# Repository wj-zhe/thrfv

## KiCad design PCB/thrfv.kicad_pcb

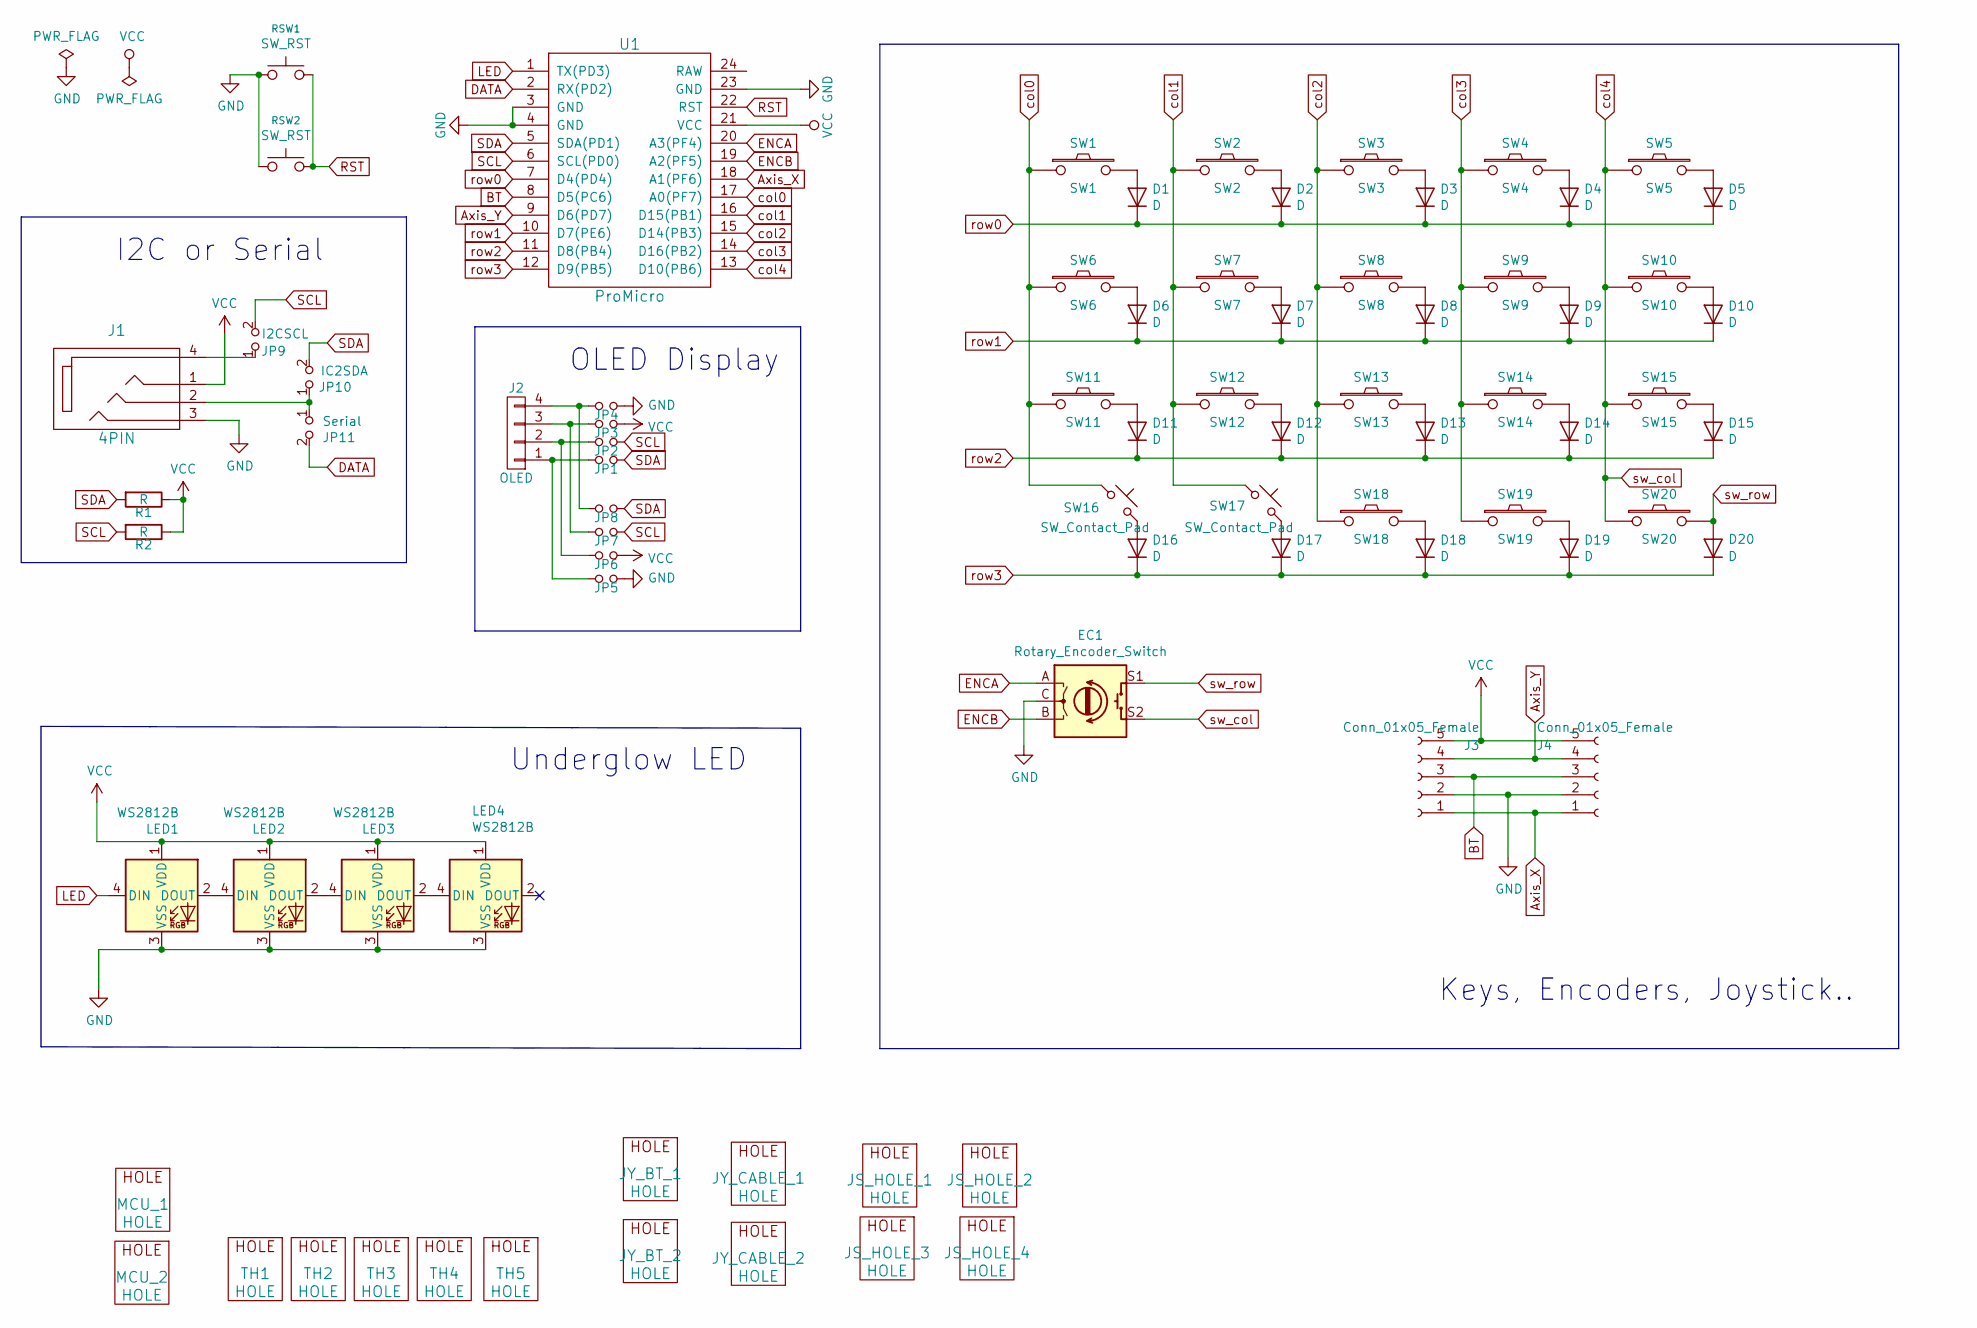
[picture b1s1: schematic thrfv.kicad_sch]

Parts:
D1, D2, D3, D4, D5, D6, D7, D8, D9, D10, D11, D12, D13, D14, D15, D16, D17, D18, D19, D20: D; Diode_SOD123_THT_2
EC1: Rotary_Encoder_Switch; RotaryEncoder_Alps_EC11E-Switch_Vertical_H20mm
J1: 4PIN; MJ-4PP-9
J2: OLED; OLED_4Pin
J3, J4: Conn_01x05_Female; TE_0-1734839-5_1x05-1MP_P0.5mm_Horizontal
JP1: JP1; SolderJumper-2_P1.3mm_Open_RoundedPad1.0x1.5mm
JP2: JP2; SolderJumper-2_P1.3mm_Open_RoundedPad1.0x1.5mm
JP3: JP3; SolderJumper-2_P1.3mm_Open_RoundedPad1.0x1.5mm
JP4: JP4; SolderJumper-2_P1.3mm_Open_RoundedPad1.0x1.5mm
JP5: JP5; SolderJumper-2_P1.3mm_Open_RoundedPad1.0x1.5mm
JP6: JP6; SolderJumper-2_P1.3mm_Open_RoundedPad1.0x1.5mm
JP7: JP7; SolderJumper-2_P1.3mm_Open_RoundedPad1.0x1.5mm
JP8: JP8; SolderJumper-2_P1.3mm_Open_RoundedPad1.0x1.5mm
JP9: I2CSCL; SolderJumper-2_P1.3mm_Open_RoundedPad1.0x1.5mm
JP10: IC2SDA; SolderJumper-2_P1.3mm_Open_RoundedPad1.0x1.5mm
JP11: Serial; SolderJumper-2_P1.3mm_Open_RoundedPad1.0x1.5mm
JS_HOLE_1, JS_HOLE_2, JS_HOLE_3, JS_HOLE_4: HOLE; MountingHole_2.7mm_M2.5
JY_BT_1, JY_BT_2: HOLE; MountingHole_3.2mm_M3
JY_CABLE_1, JY_CABLE_2: HOLE; Mounting_Hole_7x3mm
LED1, LED2, LED3, LED4: WS2812B; LED_WS2812B_PLCC4_5.0x5.0mm_P3.2mm_double_side
MCU_1, MCU_2: HOLE; MountingHole_2.2mm_M2_Pad
R1, R2: R; R_1206_DoubleSided
RSW1, RSW2: SW_RST; SW_SPST_TL3342
SW1: SW1; CherryMX_Hotswap
SW2: SW2; CherryMX_Hotswap
SW3: SW3; CherryMX_Hotswap
SW4: SW4; CherryMX_Hotswap
SW5: SW5; CherryMX_Hotswap
SW6: SW6; CherryMX_Hotswap
SW7: SW7; CherryMX_Hotswap
SW8: SW8; CherryMX_Hotswap
SW9: SW9; CherryMX_Hotswap
SW10: SW10; CherryMX_Hotswap
SW11: SW11; CherryMX_Hotswap
SW12: SW12; CherryMX_Hotswap
SW13: SW13; CherryMX_Hotswap
SW14: SW14; CherryMX_Hotswap
SW15: SW15; CherryMX_Hotswap
SW16, SW17: SW_Contact_Pad; contact_button_pad_half_circle_3mm
SW18: SW18; CherryMX_Hotswap
SW19: SW19; CherryMX_Hotswap
SW20: SW20; CherryMX_Hotswap
TH1, TH2, TH3, TH4, TH5: HOLE; MountingHole_3.2mm_M3
U1: ProMicro; ProMicro_jumper_pad_only

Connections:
Axis_X: J3.1, J4.1, U1.18 (A1(PF6))
Axis_Y: J3.4, J4.4, U1.9 (D6(PD7))
BT: J3.3, J4.3, U1.8 (D5(PC6))
DATA: JP11.2, U1.2 (RX(PD2))
ENCA: EC1.A, U1.20 (A3(PF4))
ENCB: EC1.B, U1.19 (A2(PF5))
GND: EC1.C, J1.3, J3.2, J4.2, JP4.2, JP5.2, LED1.3 (VSS), LED2.3 (VSS), LED3.3 (VSS), LED4.3 (VSS), RSW1.1, RSW2.1, U1.3 (GND), U1.4 (GND), U1.23 (GND)
LED: LED1.4 (DIN), U1.1 (TX(PD3))
unnamed: D1.2 (A), SW1.2
unnamed: D2.2 (A), SW2.2
unnamed: D3.2 (A), SW3.2
unnamed: D4.2 (A), SW4.2
unnamed: D5.2 (A), SW5.2
unnamed: D6.2 (A), SW6.2
unnamed: D7.2 (A), SW7.2
unnamed: D8.2 (A), SW8.2
unnamed: D9.2 (A), SW9.2
unnamed: D10.2 (A), SW10.2
unnamed: D11.2 (A), SW11.2
unnamed: D12.2 (A), SW12.2
unnamed: D13.2 (A), SW13.2
unnamed: D14.2 (A), SW14.2
unnamed: D15.2 (A), SW15.2
unnamed: D16.2 (A), SW16.2
unnamed: D17.2 (A), SW17.2
unnamed: D18.2 (A), SW18.2
unnamed: D19.2 (A), SW19.2
unnamed: J1.2, JP10.1, JP11.1
unnamed: J1.4, JP9.1
unnamed: J2.1, JP1.1, JP5.1
unnamed: J2.2, JP2.1, JP6.1
unnamed: J2.3, JP3.1, JP7.1
unnamed: J2.4, JP4.1, JP8.1
unnamed: LED1.2 (DOUT), LED2.4 (DIN)
unnamed: LED2.2 (DOUT), LED3.4 (DIN)
unnamed: LED3.2 (DOUT), LED4.4 (DIN)
RST: RSW1.2, RSW2.2, U1.22 (RST)
SCL: JP2.2, JP7.2, JP9.2, R2.2, U1.6 (SCL(PD0))
SDA: JP1.2, JP8.2, JP10.2, R1.2, U1.5 (SDA(PD1))
VCC: J1.1, J3.5, J4.5, JP3.2, JP6.2, LED1.1 (VDD), LED2.1 (VDD), LED3.1 (VDD), LED4.1 (VDD), R1.1, R2.1, U1.21 (VCC)
col0: SW1.1, SW6.1, SW11.1, SW16.1, U1.17 (A0(PF7))
col1: SW2.1, SW7.1, SW12.1, SW17.1, U1.16 (D15(PB1))
col2: SW3.1, SW8.1, SW13.1, SW18.1, U1.15 (D14(PB3))
col3: SW4.1, SW9.1, SW14.1, SW19.1, U1.14 (D16(PB2))
col4: EC1.S2, SW5.1, SW10.1, SW15.1, SW20.1, U1.13 (D10(PB6))
row0: D1.1 (K), D2.1 (K), D3.1 (K), D4.1 (K), D5.1 (K), U1.7 (D4(PD4))
row1: D6.1 (K), D7.1 (K), D8.1 (K), D9.1 (K), D10.1 (K), U1.10 (D7(PE6))
row2: D11.1 (K), D12.1 (K), D13.1 (K), D14.1 (K), D15.1 (K), U1.11 (D8(PB4))
row3: D16.1 (K), D17.1 (K), D18.1 (K), D19.1 (K), D20.1 (K), U1.12 (D9(PB5))
sw_row: D20.2 (A), EC1.S1, SW20.2

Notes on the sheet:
Keys, Encoders, Joystick..
OLED Display
Underglow LED
I2C or Serial

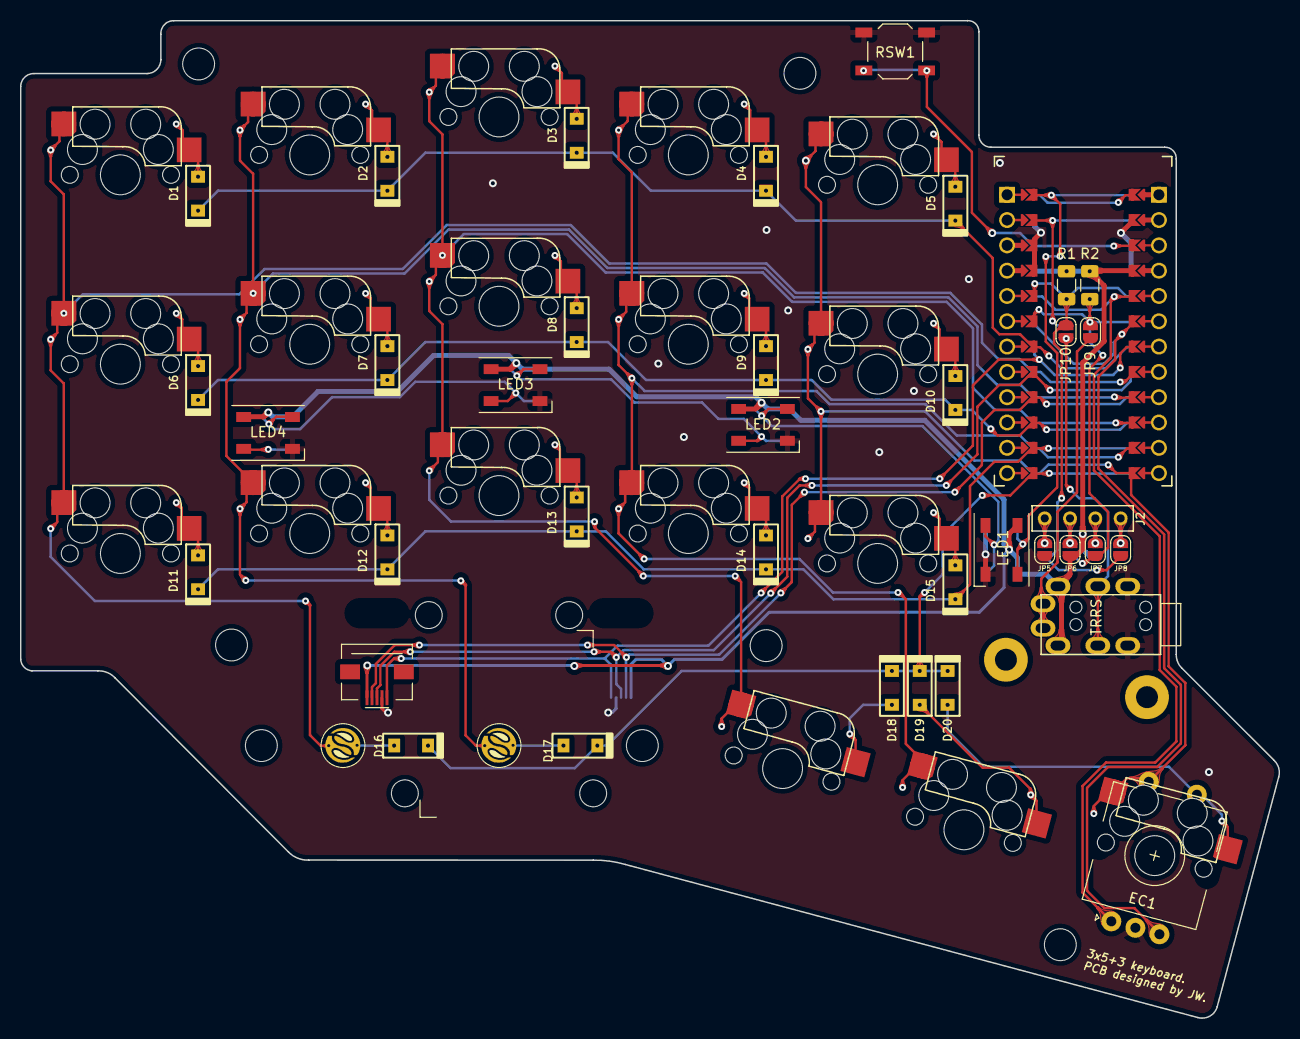
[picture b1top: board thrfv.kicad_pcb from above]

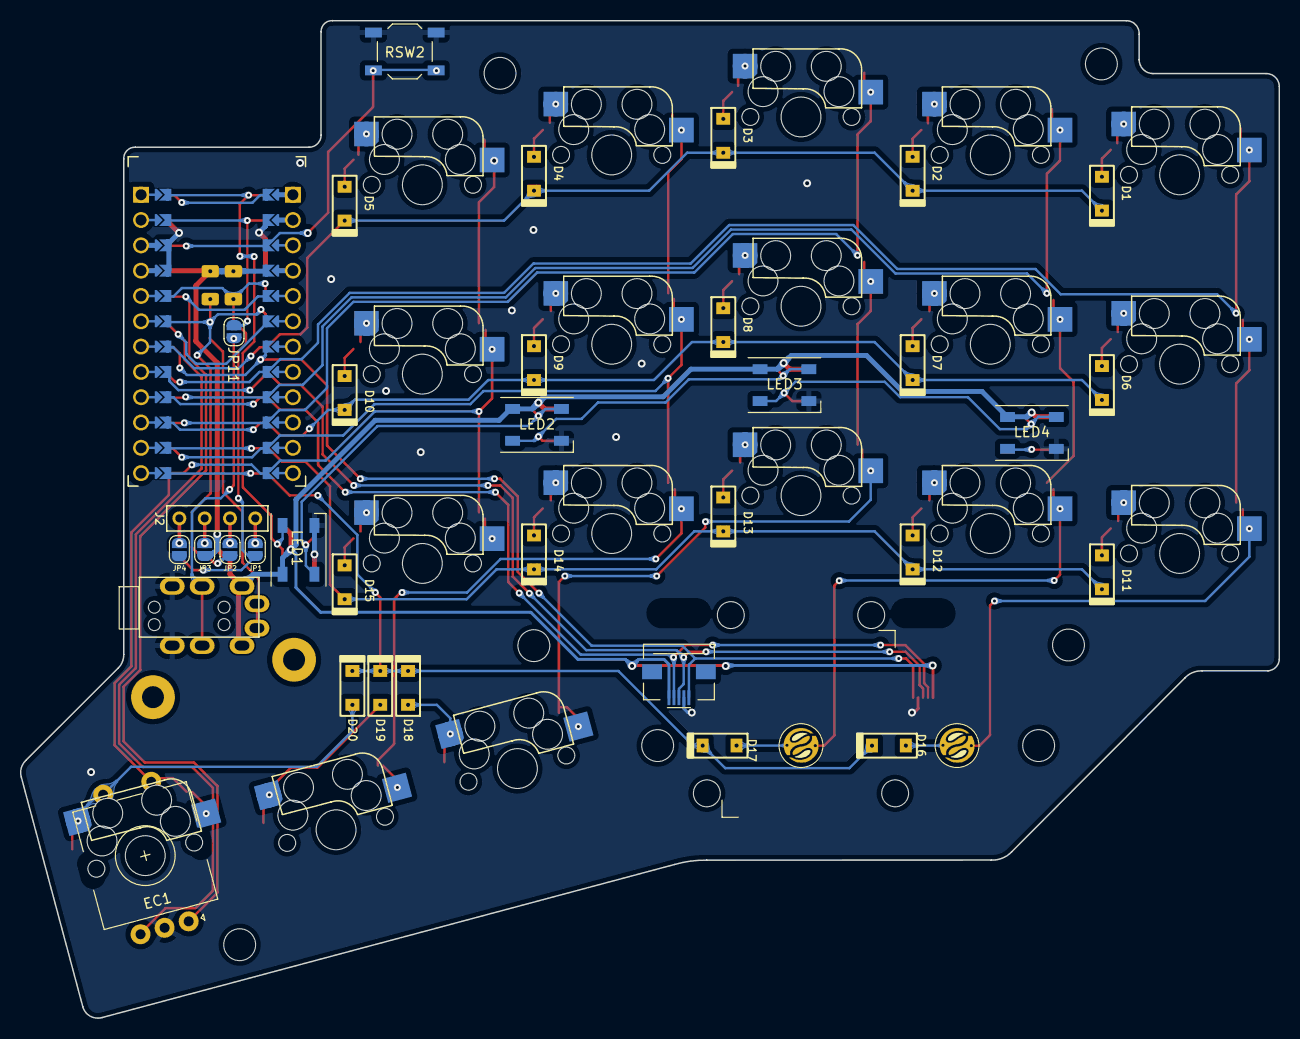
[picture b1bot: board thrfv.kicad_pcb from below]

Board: 2 copper layers, 126.3 x 100.1 mm, 80 parts (8 on the bottom side), 50 nets.

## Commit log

2022-07-06 3x5 keyboard with rotary encoder, Nintendo Switch Joystick and contact pad switches in the shape (roughly) of AT-ST (All Terrain Scout Transports).
2022-07-06 Renamed files + minor changes.
2022-07-06 Corrected Joystick cable hole error.
2022-07-06 Some more changes.
2022-07-06 Updated some footprints.
2022-07-06 1. Modified some trace and via location. 2. Included gerber files.
2022-07-08 1. Correct a serious pin allocation problem, where a digital pin was assigned for joystick Y axis. 2. Updated MX switches footprints. 3. Included flip style 5 pins FPC/FFC socket. 4. Minor changes he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
2022-07-08 Re-plotted gerber files.
2022-07-10 1. Repository renamed from AT_ST to thrfv, aka three-by-five, 3x5 2. Multiple twists.
2022-07-10 Minor changes here and there.
2022-07-14 No comment.
2022-07-17 Multiple changes. Re-plotted gerber files.
2022-07-19 First PCB production.
2022-07-22 Created files for acrylic stack case.
2023-05-11 Added firmware.
2023-05-11 Fixed bug related to encoder.h naming.
2023-07-02 Renamed some directories and files.
2023-07-30 Added media control on Layer 2, etc
2023-10-14 Updated firmware: included advanced encoder functions, etc.
2023-11-20 Updated firmware.
